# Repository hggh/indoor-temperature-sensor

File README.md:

# indoor BME280 sensor with ePaper display

  * ESP32-WROOM
  * BME280
  * 1.54" w/b epaper
  
## TODO

  * use PNP to disconnect epaper from VCC, will save ~30 µA

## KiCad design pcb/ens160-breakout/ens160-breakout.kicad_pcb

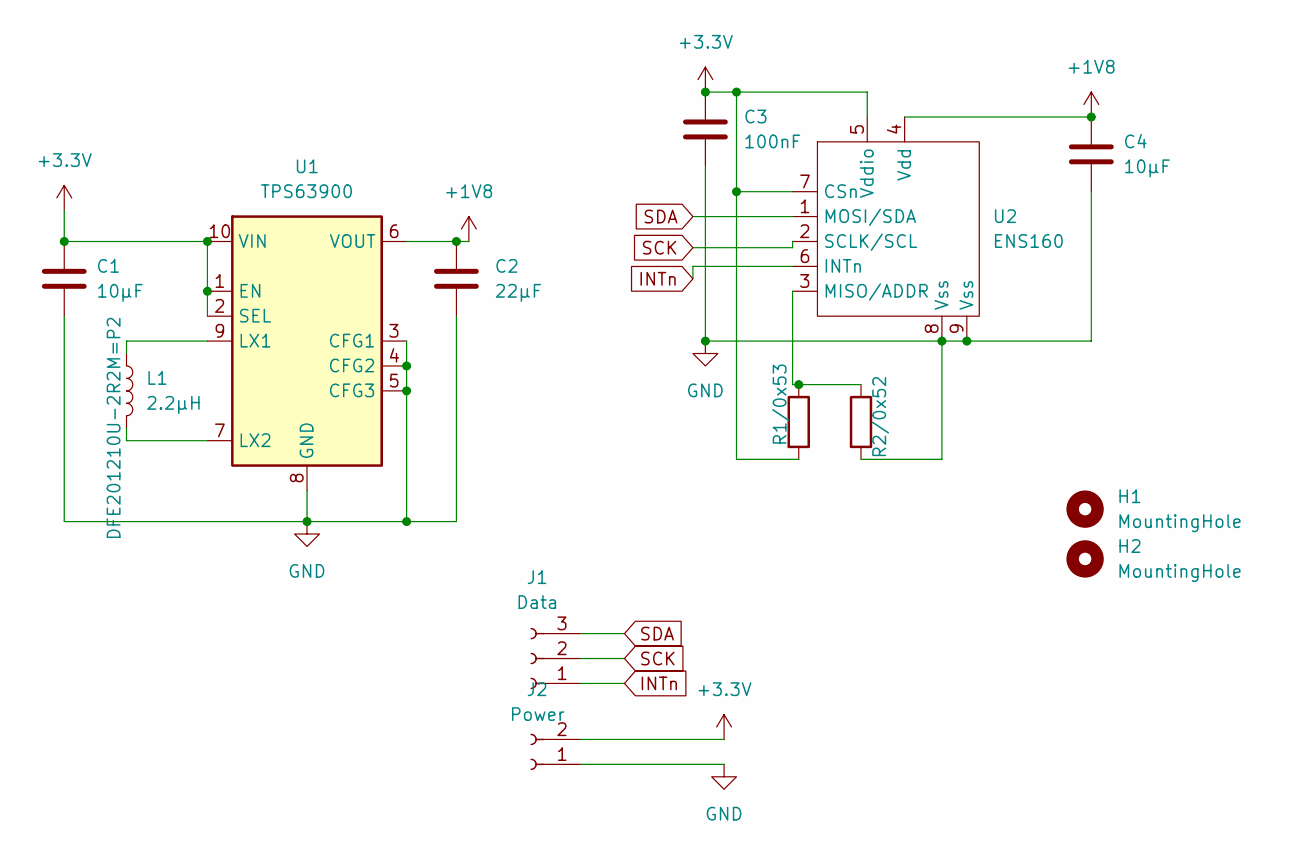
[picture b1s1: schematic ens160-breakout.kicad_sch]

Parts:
C1, C4: 10µF; C_0805_2012Metric
C2: 22µF; C_0805_2012Metric
C3: 100nF; C_0603_1608Metric
H1, H2: MountingHole; MountingHole_2.2mm_M2
J1: Data; PinHeader_1x03_P2.00mm_Vertical
J2: Power; PinHeader_1x02_P2.00mm_Vertical
L1: 2.2µH; L_0805_2012Metric
R1/0x53, R2/0x52: 0; R_0603_1608Metric_Pad0.98x0.95mm_HandSolder
U1: TPS63900; WSON-10-1EP_2.5x2.5mm_P0.5mm_EP1.2x2mm_ThermalVias
U2: ENS160

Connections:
+1V8: C2.1, C4.1, U1.6 (VOUT), U2.4 (Vdd)
+3.3V: C1.1, C3.1, J2.2, R1/0x53.2, U1.1 (EN), U1.2 (SEL), U1.10 (VIN), U2.5 (Vddio), U2.7 (CSn)
GND: C1.2, C2.2, C3.2, C4.2, J2.1, R2/0x52.2, U1.3 (CFG1), U1.4 (CFG2), U1.5 (CFG3), U1.8 (GND), U1.11 (GND), U2.8 (Vss), U2.9 (Vss)
INTn: J1.1, U2.6 (INTn)
unnamed: L1.1, U1.9 (LX1)
unnamed: L1.2, U1.7 (LX2)
unnamed: R1/0x53.1, R2/0x52.1, U2.3 (MISO/ADDR)
SCK: J1.2, U2.2 (SCLK/SCL)
SDA: J1.3, U2.1 (MOSI/SDA)

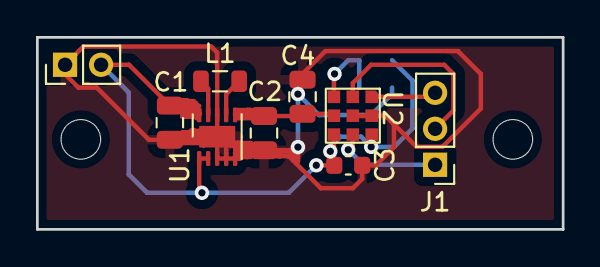
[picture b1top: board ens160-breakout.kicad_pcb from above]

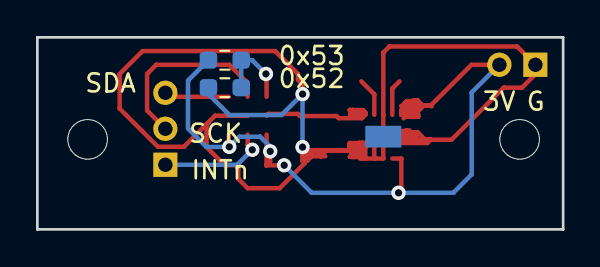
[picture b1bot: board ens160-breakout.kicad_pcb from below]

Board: 2 copper layers, 29.2 x 10.7 mm, 13 parts (2 on the bottom side), 9 nets.

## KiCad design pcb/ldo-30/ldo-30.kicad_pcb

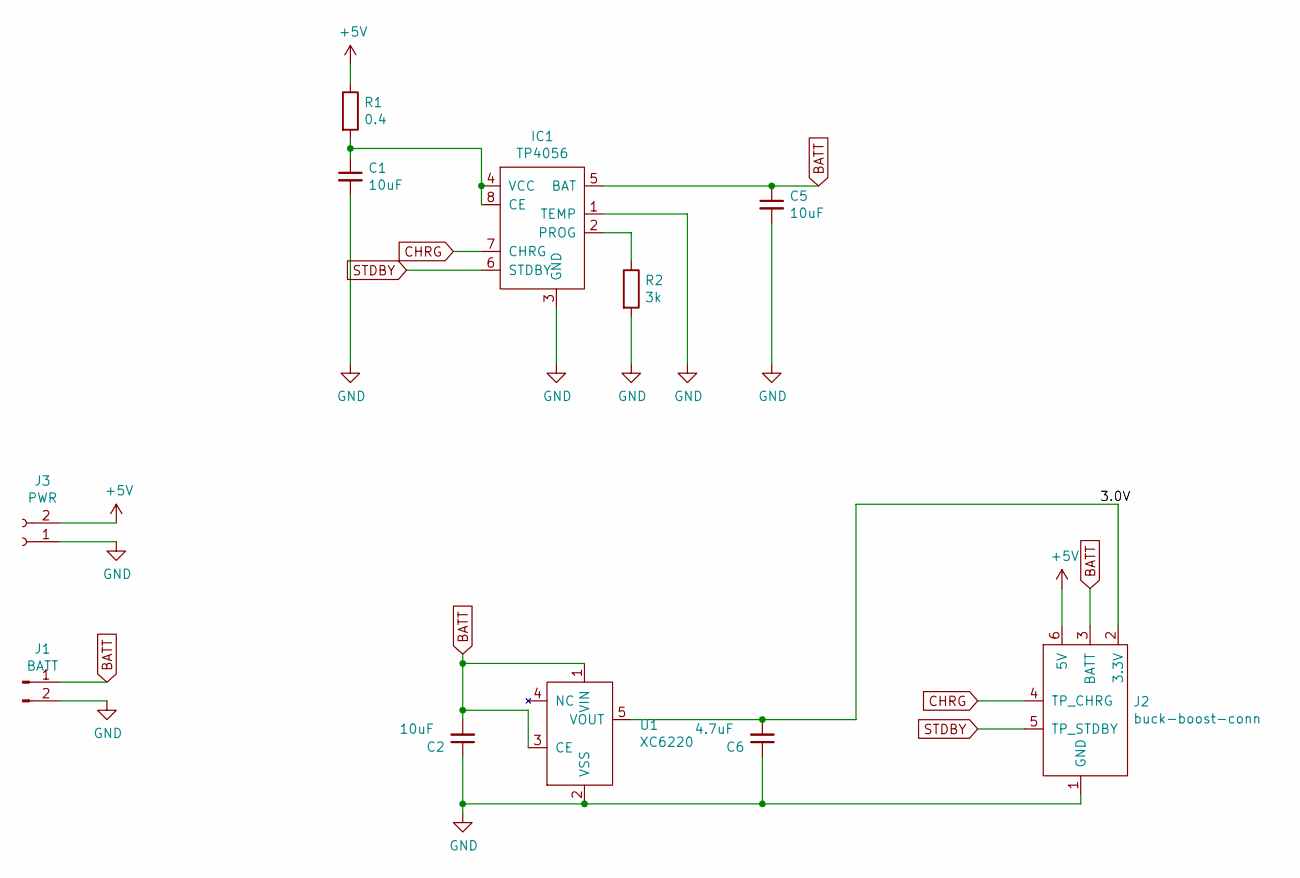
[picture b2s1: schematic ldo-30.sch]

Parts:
C1, C2, C5: 10uF; C_0805_2012Metric; LCSC C100083
C6: 4.7uF; C_0805_2012Metric; LCSC C100083
IC1: TP4056; SOIC-8_3.9x4.9mm_P1.27mm; LCSC C16581
J1: BATT; JST_PH_S2B-PH-K_1x02_P2.00mm_Horizontal
J2: buck-boost-conn
J3: PWR; PinHeader_1x02_P2.54mm_Vertical
R1: 0.4; R_0805_2012Metric; LCSC C253349
R2: 3k; R_0805_2012Metric; LCSC C17661
U1: XC6220

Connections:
+5V: J2.6 (5V), J3.2, R1.1
/3.0V: C6.2, J2.2 (3.3V), U1.5 (VOUT)
BATT: C2.2, C5.1, IC1.5 (BAT), J1.1, J2.3 (BATT), U1.1 (VIN), U1.3 (CE)
CHRG: IC1.7 (CHRG), J2.4 (TP_CHRG)
GND: C1.2, C2.1, C5.2, C6.1, IC1.1 (TEMP), IC1.3 (GND), J1.2, J2.1 (GND), J3.1, R2.2, U1.2 (VSS)
unnamed: C1.1, IC1.4 (VCC), IC1.8 (CE), R1.2
unnamed: IC1.2 (PROG), R2.1
STDBY: IC1.6 (STDBY), J2.5 (TP_STDBY)

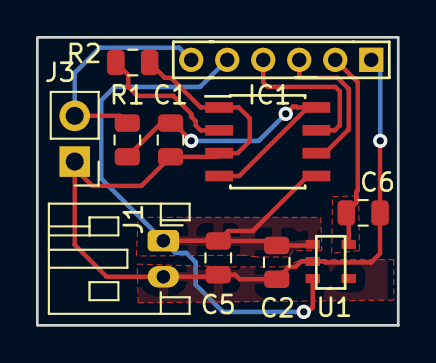
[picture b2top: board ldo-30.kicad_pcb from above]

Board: 2 copper layers, 20.0 x 16.0 mm, 11 parts (0 on the bottom side), 8 nets.

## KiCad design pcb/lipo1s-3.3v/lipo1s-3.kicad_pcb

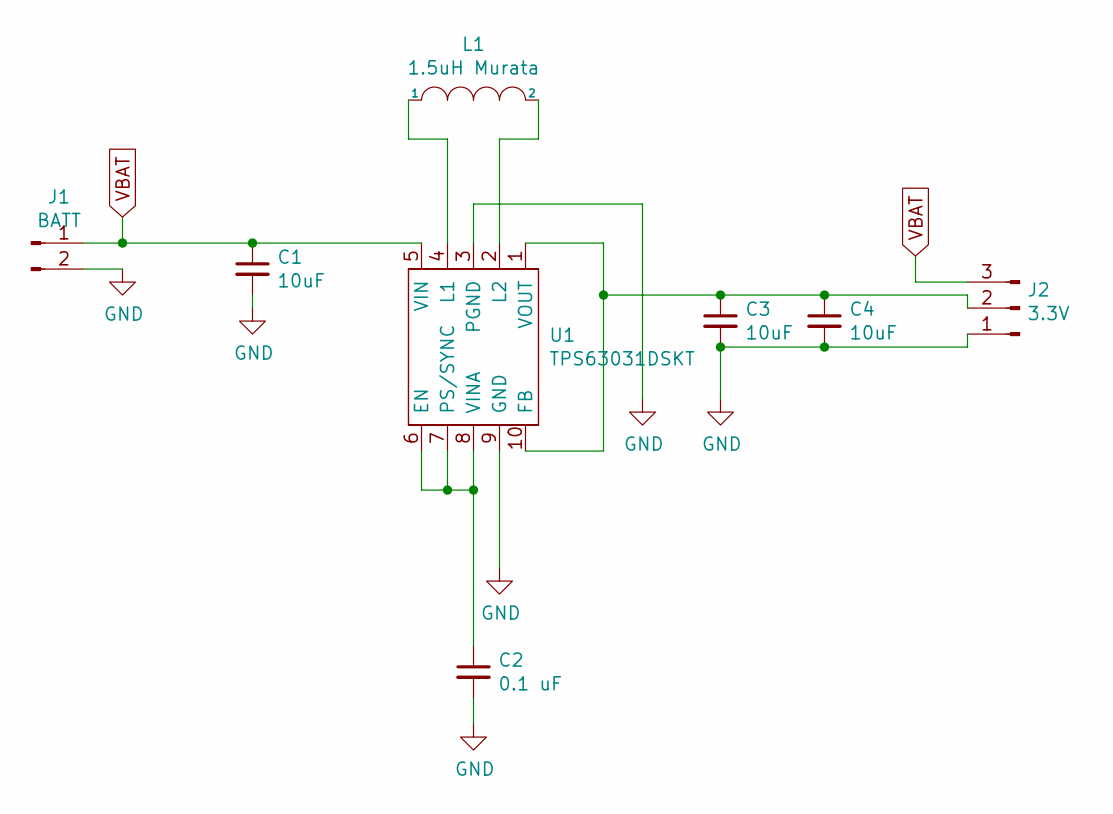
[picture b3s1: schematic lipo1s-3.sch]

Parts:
C1, C3, C4: 10uF; C_0805_2012Metric_Pad1.15x1.40mm_HandSolder
C2: 0.1 uF; C_0805_2012Metric_Pad1.15x1.40mm_HandSolder
J1: BATT; PinHeader_1x02_P2.00mm_Vertical
J2: 3.3V; PinHeader_1x03_P2.54mm_Vertical
L1: 1.5uH Murata; Murata 1266AS-H-1R5N=P2
U1: TPS63031DSKT; TPS6303x

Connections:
GND: C1.2, C2.2, C3.2, C4.2, J1.2, J2.1, U1.3 (PGND), U1.9 (GND)
unnamed: C2.1, U1.6 (EN), U1.7 (PS/SYNC), U1.8 (VINA)
unnamed: C3.1, C4.1, J2.2, U1.1 (VOUT), U1.10 (FB)
unnamed: L1.1, U1.4 (L1)
unnamed: L1.2, U1.2 (L2)
VBAT: C1.1, J1.1, J2.3, U1.5 (VIN)

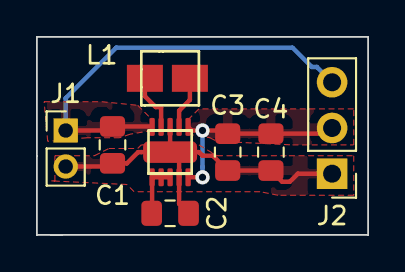
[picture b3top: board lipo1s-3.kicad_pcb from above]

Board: 2 copper layers, 18.4 x 11.0 mm, 8 parts (0 on the bottom side), 6 nets.

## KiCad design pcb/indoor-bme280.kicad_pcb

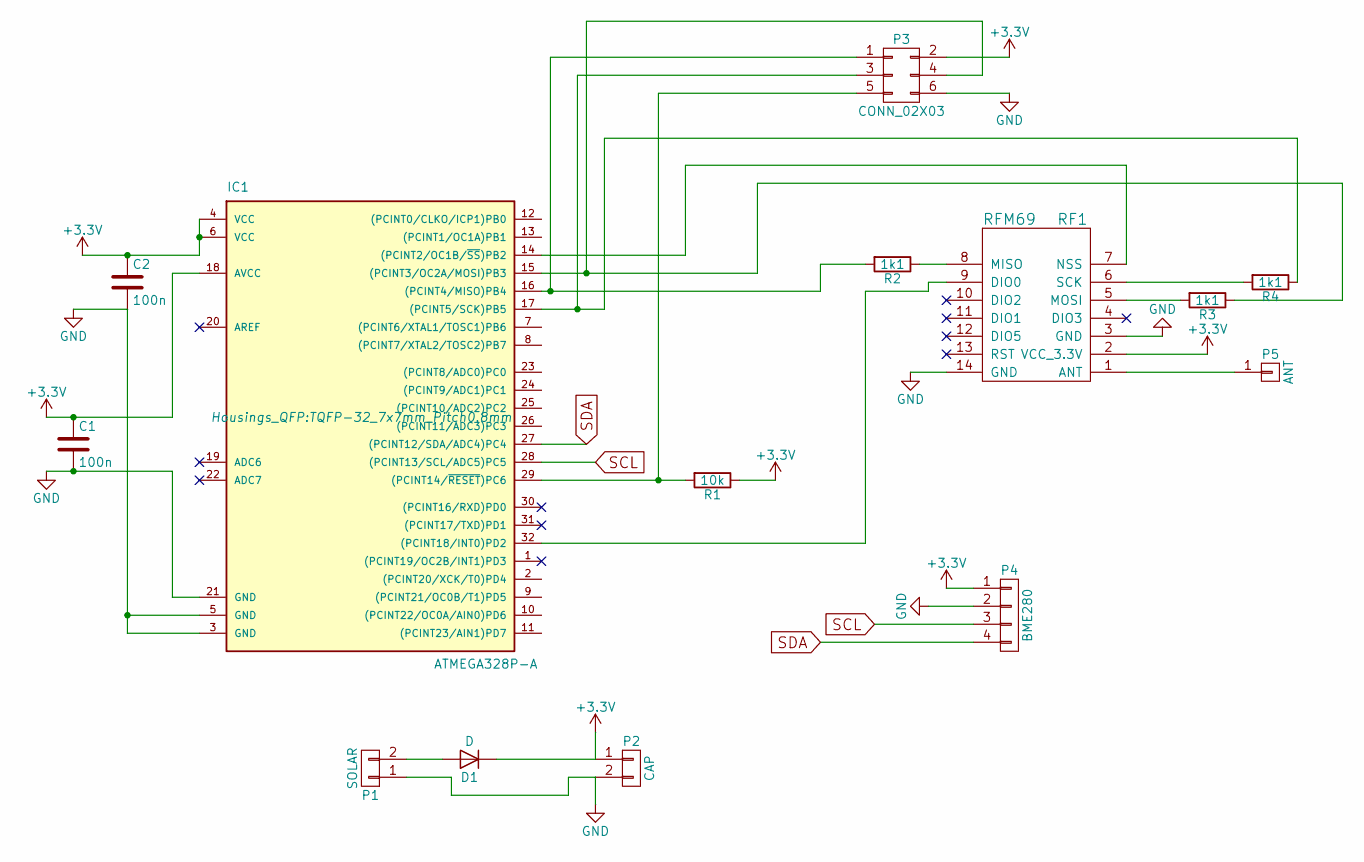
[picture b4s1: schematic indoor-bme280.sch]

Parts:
C1, C2: 100n; C_0805_HandSoldering
D1: D; Diode_DO-41_SOD81_Horizontal_RM10
IC1: ATMEGA328P-A; TQFP-32_7x7mm_Pitch0.8mm
P1: SOLAR; Pin_Header_Straight_1x02_Pitch2.00mm
P2: CAP; Pin_Header_Straight_1x02_Pitch2.00mm
P3: CONN_02X03; Pin_Header_Straight_2x03
P4: BME280; Pin_Header_Straight_1x04
P5: ANT; SolderWirePad_single_1mmDrill
R1: 10k; R_0805_HandSoldering
R2, R3, R4: 1k1; R_0805_HandSoldering
RF1: RFM69; RFM96

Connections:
+3V3: C1.1, C2.1, D1.1 (K), IC1.4 (VCC), IC1.6 (VCC), IC1.18 (AVCC), P2.1, P3.2, P4.1, R1.1, RF1.2 (VCC_3.3V)
GND: C1.2, C2.2, IC1.3 (GND), IC1.5 (GND), IC1.21 (GND), P1.1, P2.2, P3.6, P4.2, RF1.3 (GND), RF1.14 (GND)
unnamed: D1.2 (A), P1.2
unnamed: IC1.14 ((PCINT2/OC1B/~SS~)PB2), RF1.7 (NSS)
unnamed: IC1.15 ((PCINT3/OC2A/MOSI)PB3), P3.4, R3.1
unnamed: IC1.16 ((PCINT4/MISO)PB4), P3.1, R2.2
unnamed: IC1.17 ((PCINT5/SCK)PB5), P3.3, R4.1
unnamed: IC1.29 ((PCINT14/~RESET~)PC6), P3.5, R1.2
unnamed: IC1.32 ((PCINT18/INT0)PD2), RF1.9 (DIO0)
unnamed 27: P5.1, RF1.1 (ANT); also elsewhere on the board
unnamed: R2.1, RF1.8 (MISO)
unnamed: R3.2, RF1.5 (MOSI)
unnamed: R4.2, RF1.6 (SCK)
SCL: IC1.28 ((PCINT13/SCL/ADC5)PC5), P4.3
SDA: IC1.27 ((PCINT12/SDA/ADC4)PC4), P4.4

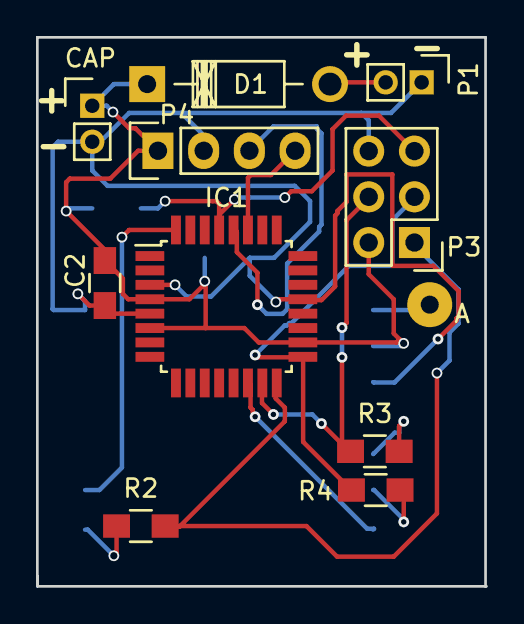
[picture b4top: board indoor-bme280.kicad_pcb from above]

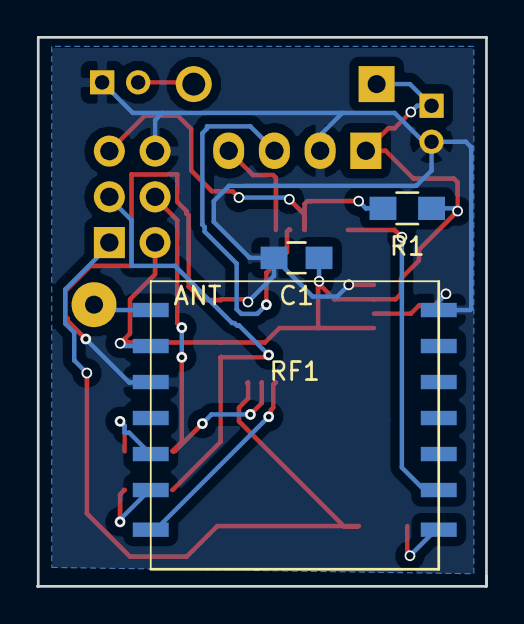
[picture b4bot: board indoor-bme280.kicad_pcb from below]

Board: 2 copper layers, 24.9 x 30.5 mm, 14 parts (3 on the bottom side), 15 nets.

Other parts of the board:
A: ANT; SolderWirePad_single_1mmDrill

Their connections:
unnamed 27: A.1; also elsewhere on the board

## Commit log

2018-06-15 added pcb
2018-06-15 added platformio stuff
2018-06-15 updated gitignore
2018-06-15 added initial code
2018-06-18 fixed sleep code, fixed sprintf
2018-06-18 updated kicad
2018-06-18 fixed modulo
2018-06-19 add 10ms delay time
2018-06-22 add rfm library
2018-06-22 added pics
2018-06-22 added example config.h
2018-09-25 added solar holder
2018-09-28 wait longer before retransmit
2018-11-01 tell BME280 to read temp/hum before the last sleep of 1m
2018-11-08 full case for solar panels
2018-11-08 added stl
2018-11-19 more space for the wires
2018-11-26 updated stl
2018-12-16 added pic of solar case
2018-12-28 moved to external Voltage lib
2020-02-28 change to ESP32 - wip
2020-02-28 use arduino String library and c_str()
2020-06-05 new wip code
2020-06-06 use esp32 blue disable functions, remove event probelms with mqtt
2020-06-06 do not send data if wakeup via touchpad, after touch setup new sleep time
2020-06-11 flush is already called by mqtt disconnect
2020-06-12 add bitmaps and gimp source of battery icons
2020-06-12 rename icons
2020-06-12 add extra lib for voltage divider
2020-06-12 wip: tp4056 readings, voltage divider, corret sleep time
2020-06-16 change pin out for enable voltage divider
2020-06-19 lower cpu freq, lower power usage
2020-06-19 add 1. version of pcbs
2020-06-21 add led output for possible light after touch event
2020-07-02 rework with new footprints
2020-07-03 add LCSC part numbers, use another coil
2020-07-03 back to marata inductor; smaller pcb
2020-07-14 change to SparkFun with sleep mode for bme280: deep sleep power consumption from 500uA to ~45uA
2020-07-23 add test pcb with LDO 3.0V XC6220 lipo and tp4056 charger ic
2020-07-23 updated footprint
2020-07-29 update todo
2022-10-23 remove old unused pcbs
2023-10-07 add ens160er breakout
